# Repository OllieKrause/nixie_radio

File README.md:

# nixie_radio
A simple FM radio that uses nixie tubes to display frequency and volume. The radio does use a custom PCB so I've included the Autodesk Eagle .brd, .sch, and custom.lib files. I also included the CAM files which are compatible with JLCPCB's cheapest 2 layer PCB manufacturing service.

I want to give a huge thanks to andykarpov for his TEA5767 FM radio library which I've used extensively throughout this project. https://github.com/andykarpov/TEA5767

While the code and hardware have been tested, this project is still very much a work in progress and the user experience has yet to be optimized. 

I hope to document this project in much greater detail once I'm satisfied with the first prototype. 

Questions, comments, suggestions?
Ollie.krause@gmail.com
https://bananascience.net

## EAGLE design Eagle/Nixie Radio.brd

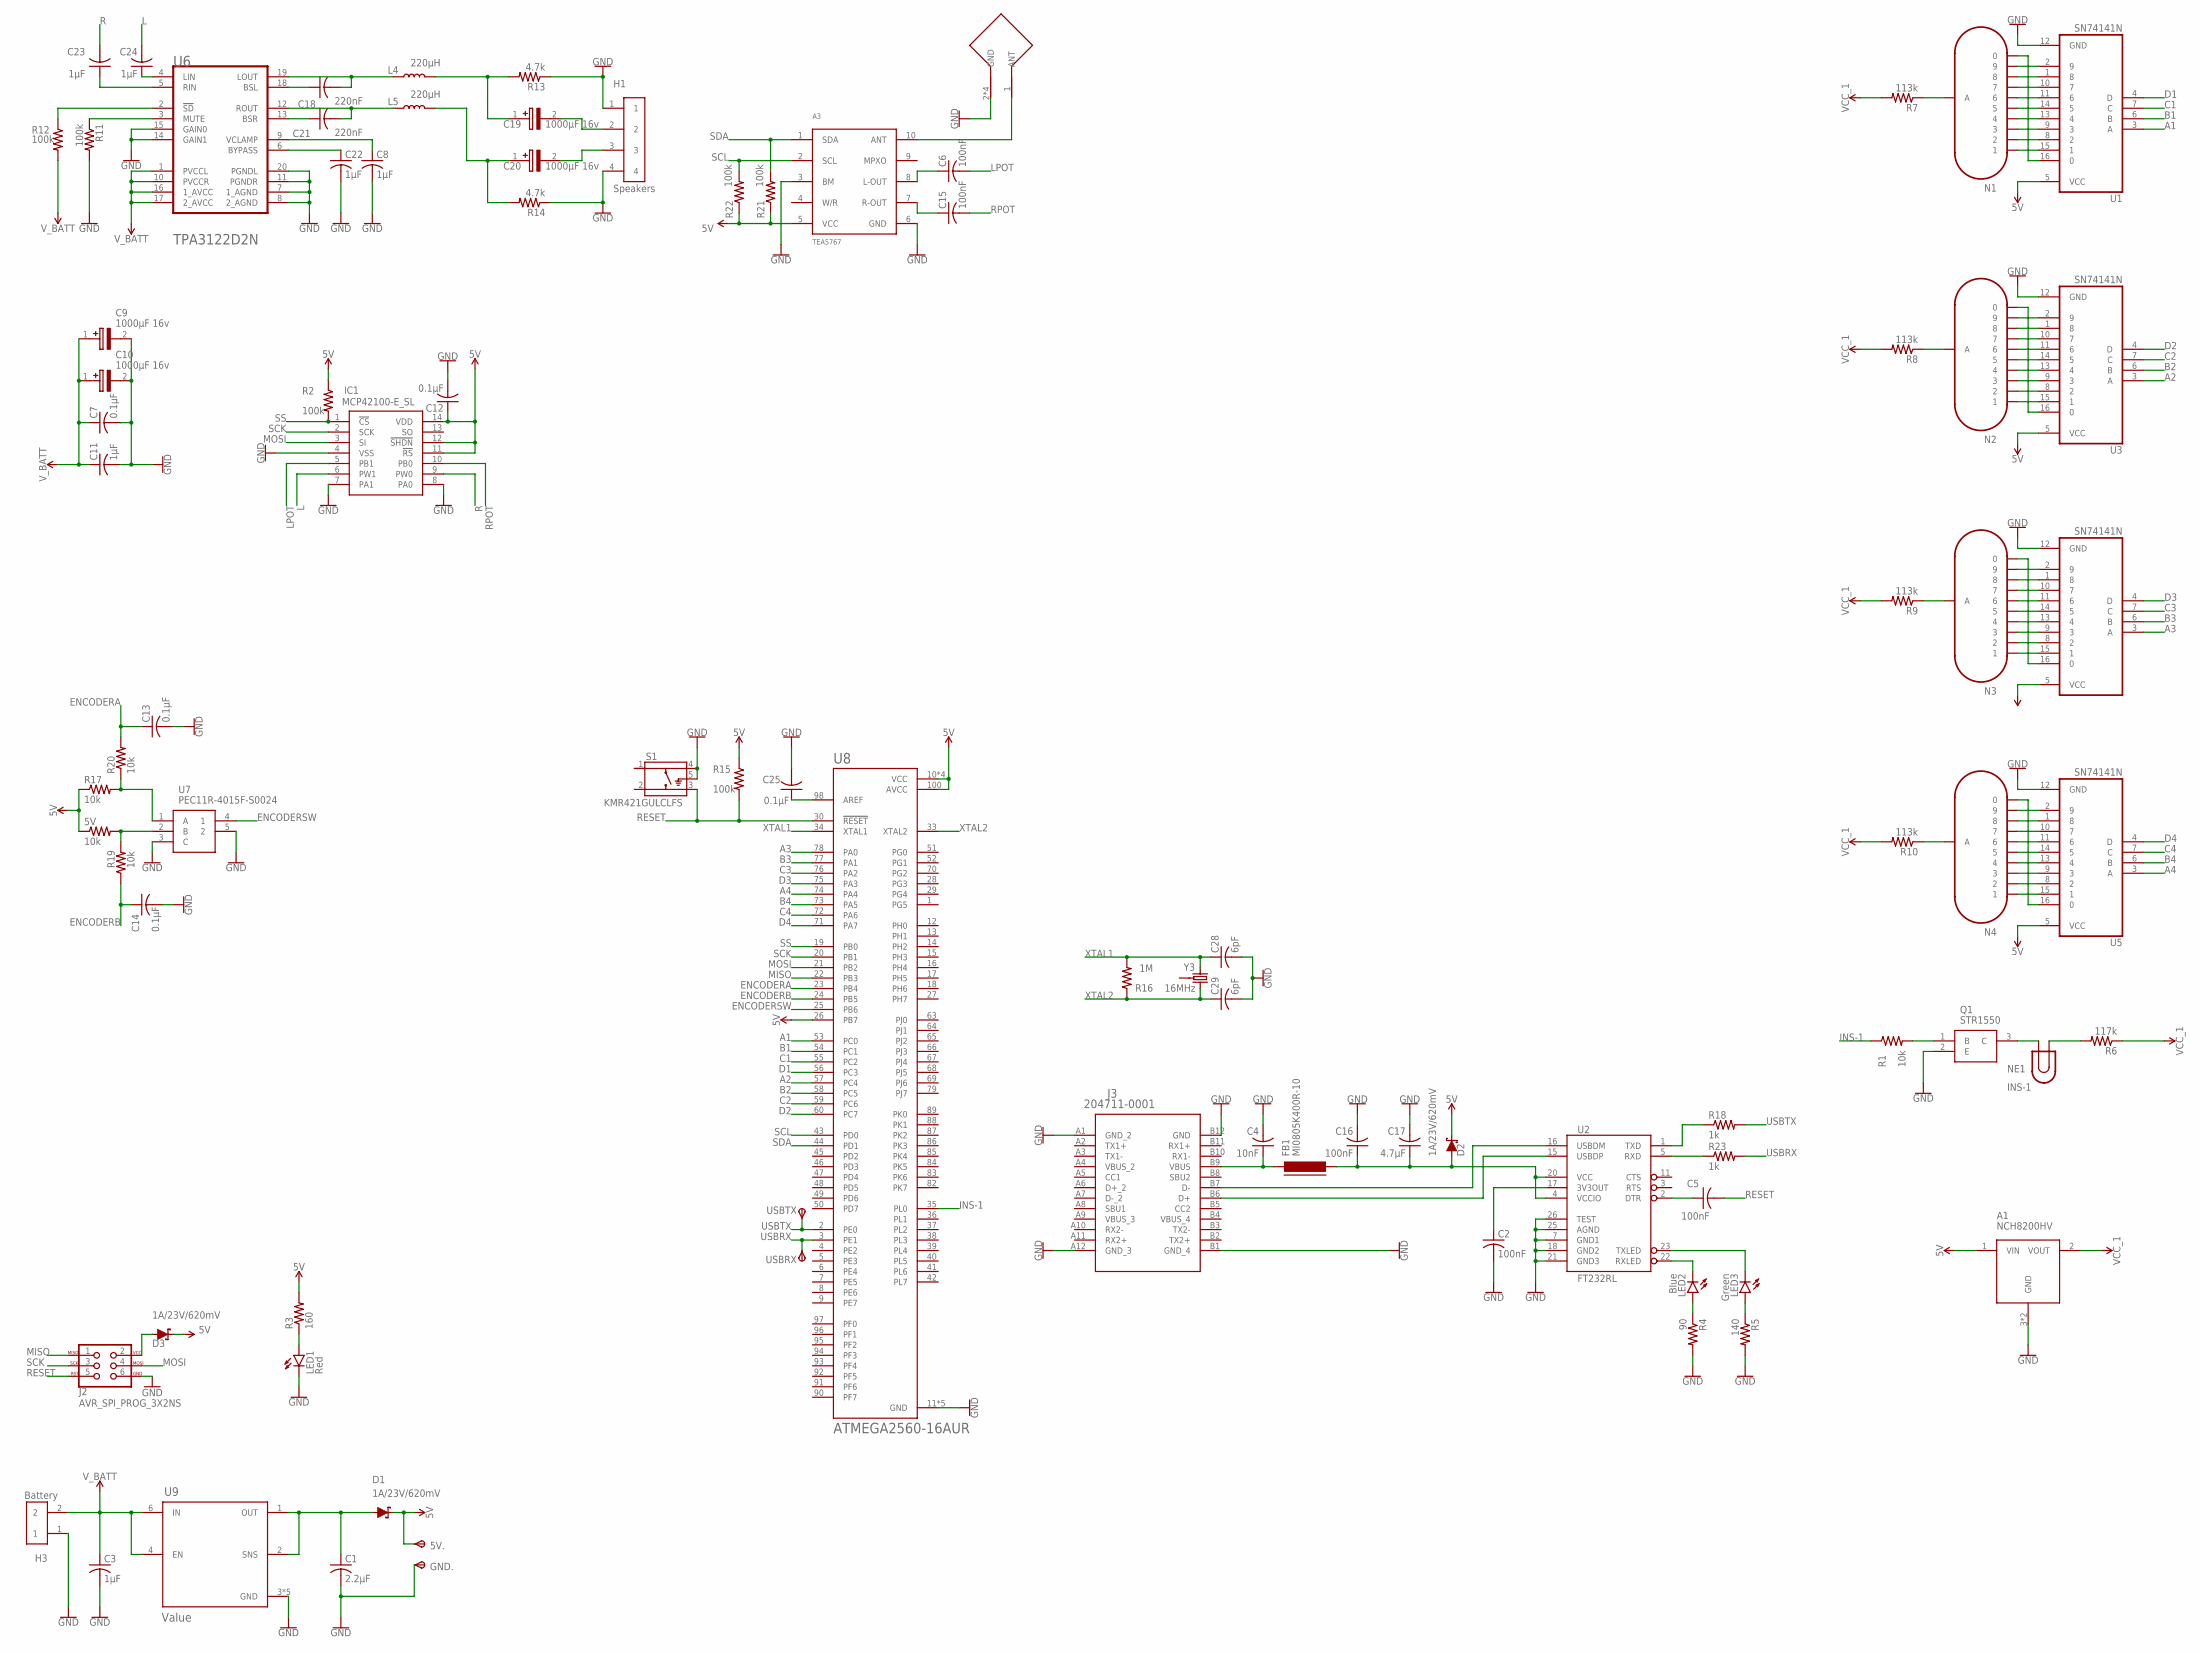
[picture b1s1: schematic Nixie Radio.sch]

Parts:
5V: 10k; M0805
5V.: TPSTP20R; TP20R
A1: NCH8200HV
A3: TEA5767
AE1: ANTENNA; RFPC-MMCX03-F
C1: 2.2µF; C0805
C2, C5, C6, C15, C16: 100nF; C0805
C3, C8, C11, C22, C23, C24: 1µF; C0805
C4: 10nF; C0805
C7, C12, C13, C14, C25: 0.1µF; C0805
C9, C10, C19, C20: 1000µF 16v; CAPAE1030X1080N
C17: 4.7µF; C0805
C18, C21: 220nF; C0805
C28, C29: 6pF; C0805
D1, D2, D3: 1A/23V/620mV; SOD-323
FB1: MI0805K400R-10; FB805
GND.: TPSTP20R; TP20R
H1: Speakers; 4_PAD_0.1"
H3: Battery; 2_PAD_0.1"
IC1: MCP42100-E_SL; SOIC127P600X175-14N
J2: AVR_SPI_PROG_3X2NS; 2X3-NS
J3: 204711-0001; 204711-0001_MOL
L4, L5: 220µH; 0207ROUND
LED1: Red; SML0805
LED2: Blue; SML0805
LED3: Green; SML0805
N1, N2, N3, N4: IN-17
NE1: INS-1
Q1: STR1550; SOT105P255X140-3N
R1, R17, R19, R20: 10k; M0805
R2, R11, R12, R15, R21, R22: 100k; M0805
R3: 160; M0805
R4: 90; M0805
R5: 140; M0805
R6: 117k; M0805
R7, R8, R9, R10: 113k; M0805
R13, R14: 4.7k; M0805
R16: 1M; M0805
R18, R23: 1k; M0805
S1: KMR421GULCLFS; SW_KMR421GULCLFS
U1, U3, U4, U5: SN74141N; DIP762W46P254L2134H508Q16
U2: FT232RL; SSOP28DB
U6: TEXAS_INSTRUMENTS_TPA3122D2NTEXAS_INSTRUMENTS_TPA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; TEXAS_INSTRUMENTS_TPA3122D2N_0
U7: PEC11R-4015F-S0024; PEC12R-4XXXF-SXXXX_1
U8: ATMEGA2560-16AUR; QFP50P1600X1600X120-100N
U9: Value; 6-WSON
USBRX: TPSTP20R; TP20R
USBTX: TPSTP20R; TP20R
Y3: 16MHz; CRYSTAL-SMD-2X2.5MM

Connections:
5V: 5V.1, 5V..TP, A1.1 (VIN), A3.5 (VCC), C12.1, D1.C, D2.C, D3.C, IC1.11 (!RS), IC1.12 (!SHDN), IC1.14 (VDD), R2.1, R3.2, R15.1, R17.1, R21.1, R22.1, U1.5 (VCC), U3.5 (VCC), U4.5 (VCC), U5.5 (VCC), U8.10 (VCC), U8.26 (PB7), U8.31 (VCC), U8.61 (VCC), U8.80 (VCC), U8.100 (AVCC)
A1: U1.3 (A), U8.53 (PC0)
A2: U3.3 (A), U8.57 (PC4)
A3: U4.3 (A), U8.78 (PA0)
A4: U5.3 (A), U8.74 (PA4)
B1: U1.6 (B), U8.54 (PC1)
B2: U3.6 (B), U8.58 (PC5)
B3: U4.6 (B), U8.77 (PA1)
B4: U5.6 (B), U8.73 (PA5)
C1: U1.7 (C), U8.55 (PC2)
C2: U3.7 (C), U8.59 (PC6)
C3: U4.7 (C), U8.76 (PA2)
C4: U5.7 (C), U8.72 (PA6)
D1: U1.4 (D), U8.56 (PC3)
D2: U3.4 (D), U8.60 (PC7)
D3: U4.4 (D), U8.75 (PA3)
D4: U5.4 (D), U8.71 (PA7)
ENCODERA: C13.1, R20.2, U8.23 (PB4)
ENCODERB: C14.1, R19.1, U8.24 (PB5)
ENCODERSW: U7.4 (1), U8.25 (PB6)
GND: A1.3 (GND), A1.4 (GND), A3.3 (BM), A3.6 (GND), AE1.2 (GND), AE1.3 (GND), AE1.4 (GND), AE1.5 (GND), C1.2, C2.2, C3.2, C4.2, C7.2, C8.2, C9.2 (-), C10.2 (-), C11.2, C12.2, C13.2, C14.2, C16.2, C17.2, C22.2, C25.2, C28.2, C29.2, GND..TP, H1.1, H1.4, H3.1, IC1.4 (VSS), IC1.7 (PA1), IC1.8 (PA0), J2.6, J3.A1 (GND_2), J3.A12 (GND_3), J3.B1 (GND_4), J3.B12 (GND), LED1.C, Q1.2 (E), R4.2, R5.2, R11.2, R13.1, R14.1, S1.4, S1.5 (G), U1.12 (GND), U2.7 (GND1), U2.18 (GND2), U2.21 (GND3), U2.25 (AGND), U2.26 (TEST), U3.12 (GND), U4.12 (GND), U5.12 (GND), U6.7 (1_AGND), U6.8 (2_AGND), U6.11 (PGNDR), U6.14 (GAIN1), U6.15 (GAIN0), U6.20 (PGNDL), U7.3 (C), U7.5 (2), U8.11 (GND), U8.32 (GND), U8.62 (GND), U8.81 (GND), U8.99 (GND), U9.3 (GND), U9.5 (GND), U9.7 (GND), U9.8 (GND), U9.9 (GND), Y3.P2 (GND), Y3.P4 (GND)
INS-1: R1.1, U8.35 (PL0)
L: C24.2, IC1.6 (PW1)
LPOT: C6.2, IC1.5 (PB1)
MISO: J2.1, U8.22 (PB3)
MOSI: IC1.3 (SI), J2.4, U8.21 (PB2)
unnamed: C4.1, FB1.1, J3.B9 (VBUS)
unnamed: NE1.2, Q1.3 (C)
unnamed: NE1.1, R6.2
unnamed: C5.1, U2.2 (DTR)
unnamed: C2.1, U2.17 (3V3OUT)
unnamed: LED1.A, R3.1
unnamed: C16.1, C17.1, D2.A, FB1.2, U2.4 (VCCIO), U2.20 (VCC)
unnamed: C1.1, D1.A, U9.1 (OUT), U9.2 (SNS)
unnamed: Q1.1 (B), R1.2
unnamed: N1.1, U1.15 (1)
unnamed: J3.B6 (D+), U2.15 (USBDP)
unnamed: J3.B7 (D-), U2.16 (USBDM)
unnamed: R18.1, U2.1 (TXD)
unnamed: N1.2, U1.8 (2)
unnamed: N1.3, U1.9 (3)
unnamed: N1.4, U1.13 (4)
unnamed: N1.5, U1.14 (5)
unnamed: N1.6, U1.11 (6)
unnamed: N1.7, U1.10 (7)
unnamed: N1.8, U1.1 (8)
unnamed: N1.9, U1.2 (9)
unnamed: N1.0, U1.16 (0)
unnamed: N1.A, R7.1
unnamed: N2.1, U3.15 (1)
unnamed: N2.2, U3.8 (2)
unnamed: N2.3, U3.9 (3)
unnamed: N2.4, U3.13 (4)
unnamed: N2.5, U3.14 (5)
unnamed: N2.6, U3.11 (6)
unnamed: N2.7, U3.10 (7)
unnamed: N2.8, U3.1 (8)
unnamed: N2.9, U3.2 (9)
unnamed: N2.0, U3.16 (0)
unnamed: N2.A, R8.1
unnamed: N3.1, U4.15 (1)
unnamed: N3.2, U4.8 (2)
unnamed: N3.3, U4.9 (3)
unnamed: N3.4, U4.13 (4)
unnamed: N3.5, U4.14 (5)
unnamed: N3.6, U4.11 (6)
unnamed: N3.7, U4.10 (7)
unnamed: N3.8, U4.1 (8)
unnamed: N3.9, U4.2 (9)
unnamed: N3.0, U4.16 (0)
unnamed: N3.A, R9.1
unnamed: N4.1, U5.15 (1)
unnamed: N4.2, U5.8 (2)
unnamed: N4.3, U5.9 (3)
unnamed: N4.4, U5.13 (4)
unnamed: N4.5, U5.14 (5)
unnamed: N4.6, U5.11 (6)
unnamed: N4.7, U5.10 (7)
unnamed: N4.8, U5.1 (8)
unnamed: N4.9, U5.2 (9)
unnamed: N4.0, U5.16 (0)
unnamed: N4.A, R10.1
unnamed: LED2.A, R4.1
unnamed: C8.1, U6.9 (VCLAMP)
unnamed: A3.10 (ANT), AE1.1 (ANT)
unnamed: R11.1, U6.3 (MUTE)
unnamed: R12.1, U6.2 (!SD!)
unnamed: R23.1, U2.5 (RXD)
unnamed: C18.2, L4.1, U6.19 (LOUT)
unnamed: C18.1, U6.18 (BSL)
unnamed: C19.2 (-), H1.2
unnamed: C20.1 (+), L5.2, R14.2
unnamed: C20.2 (-), H1.3
unnamed: C21.1, U6.13 (BSR)
unnamed: LED2.C, U2.22 (RXLED)
unnamed: C22.1, U6.6 (BYPASS)
unnamed: C23.1, U6.5 (RIN)
unnamed: C24.1, U6.4 (LIN)
unnamed: C19.1 (+), L4.2, R13.2
unnamed: C21.2, L5.1, U6.12 (ROUT)
unnamed: LED3.C, U2.23 (TXLED)
unnamed: C25.1, U8.98 (AREF)
unnamed: R17.2, R20.1, U7.1 (A)
unnamed: LED3.A, R5.1
unnamed: 5V.2, R19.2, U7.2 (B)
unnamed: A3.8 (L-OUT), C6.1
unnamed: A3.7 (R-OUT), C15.1
unnamed: D3.A, J2.2
R: C23.2, IC1.9 (PW0)
RESET: C5.2, J2.5, R15.2, S1.3, U8.30 (!RESET)
RPOT: C15.2, IC1.10 (PB0)
SCK: IC1.2 (SCK), J2.3, U8.20 (PB1)
SCL: A3.2 (SCL), R22.2, U8.43 (PD0)
SDA: A3.1 (SDA), R21.2, U8.44 (PD1)
SS: IC1.1 (!CS), R2.2, U8.19 (PB0)
USBRX: R23.2, U8.3 (PE1), USBRX.TP
USBTX: R18.2, U8.2 (PE0), USBTX.TP
VBUS_2: J3.A4 (VBUS_2)
VBUS_3: J3.A9 (VBUS_3)
VBUS_4: J3.B4 (VBUS_4)
VCC_1: A1.2 (VOUT), R6.1, R7.2, R8.2, R9.2, R10.2
V_BATT: C3.1, C7.1, C9.1 (+), C10.1 (+), C11.1, H3.2, R12.2, U6.1 (PVCCL), U6.10 (PVCCR), U6.16 (1_AVCC), U6.17 (2_AVCC), U9.4 (EN), U9.6 (IN)
XTAL1: C28.1, R16.2, U8.34 (XTAL1), Y3.P1 (1)
XTAL2: C29.1, R16.1, U8.33 (XTAL2), Y3.P3 (2)

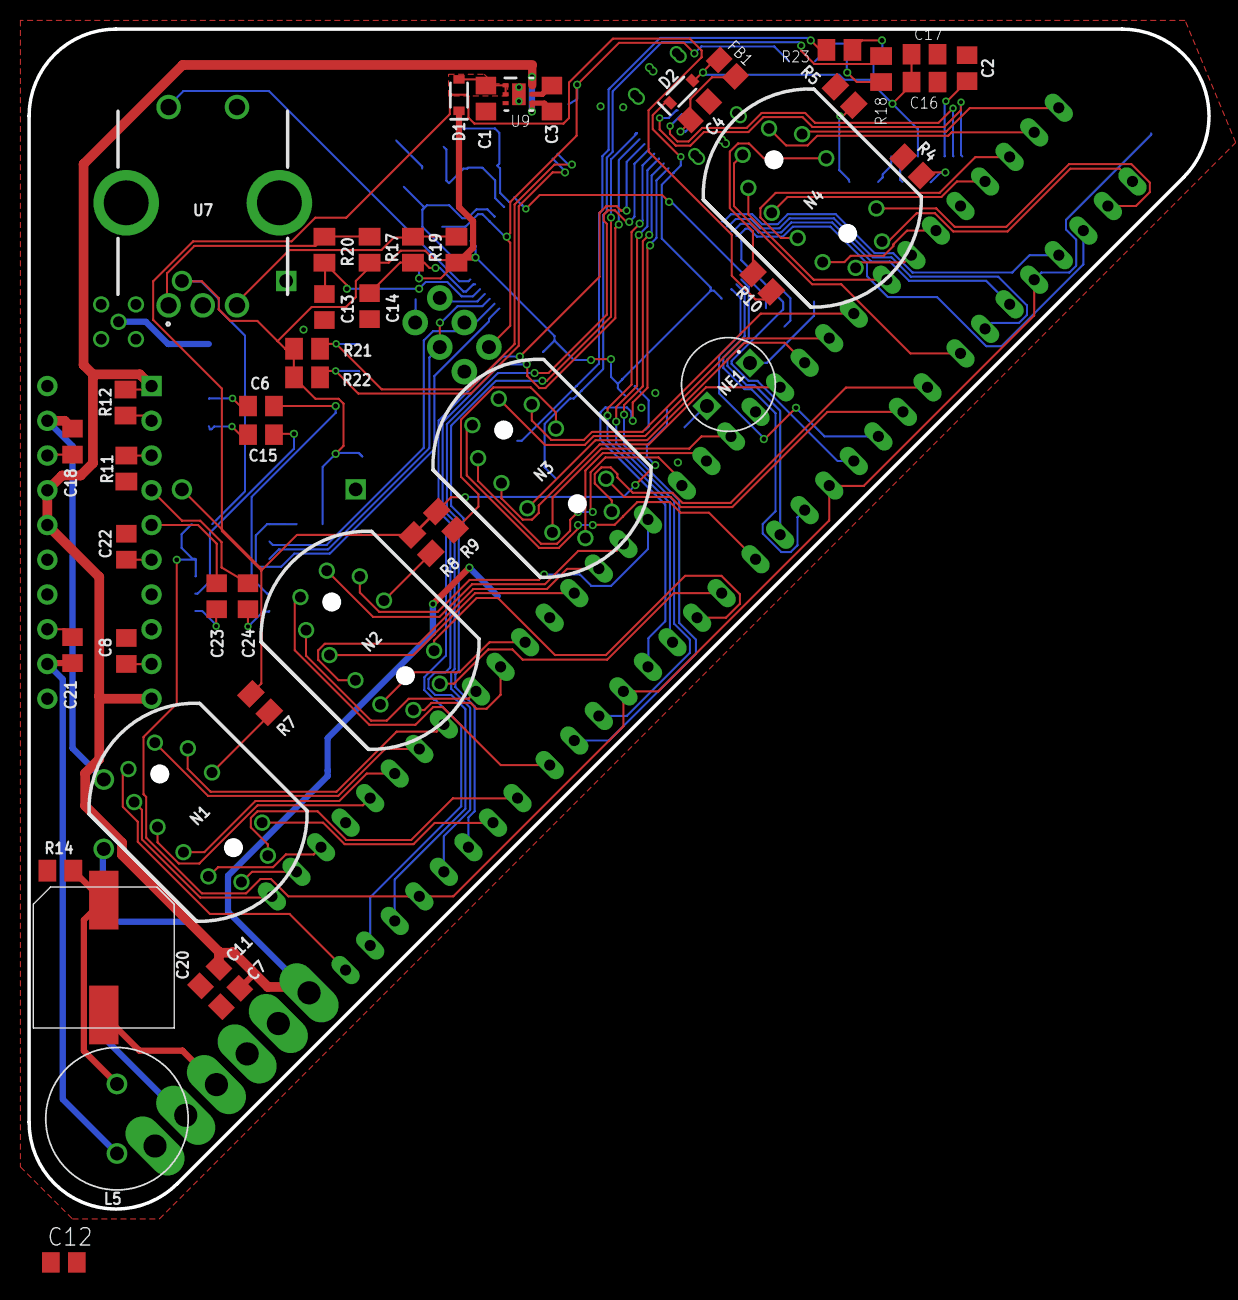
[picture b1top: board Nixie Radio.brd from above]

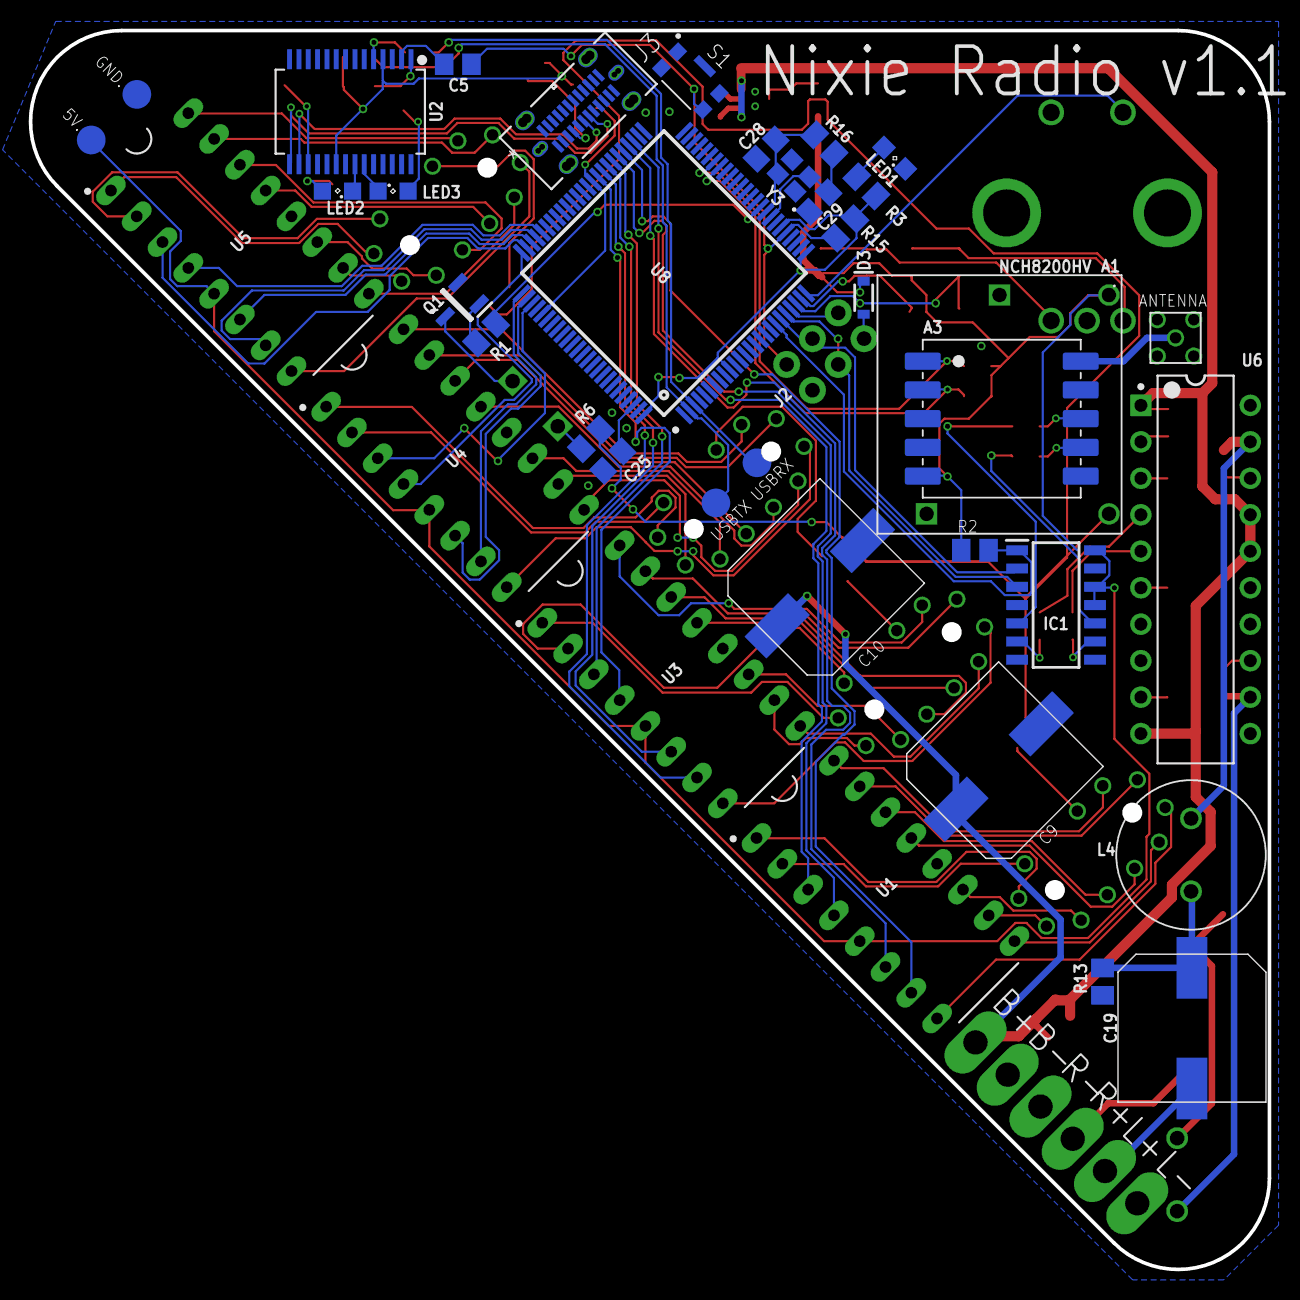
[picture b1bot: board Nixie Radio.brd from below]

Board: 2 copper layers, 86.3 x 86.3 mm, 89 parts (41 on the bottom side), 121 nets.

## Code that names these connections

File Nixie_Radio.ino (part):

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#include <SPI.h>

// Rotary encoder inputs
#define encoderA 10
#define encoderB 11
#define encoderSW 12

// Number of nixie tubes (number of digits)
#define digits 4
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
  changeFrequency(); // Tune radio to recovered frequency

  pinMode(encoderA, INPUT); // Set encoder pins as inputs
  pinMode(encoderB, INPUT);
  pinMode(encoderSW, INPUT_PULLUP);

  pinMode(potCs, OUTPUT); // Configure pot chip select as output
  digitalWrite(potCs, HIGH); // Pot chip select default to de-selected
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

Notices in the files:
Nixie_Radio.ino:
License: Creative Commons Non Commercial
parts and their libraries:
SparkFun-Connectors: Licensing: Creative Commons ShareAlike 4.0 International - https://creativecommons.org/licenses/by-sa/4.0
COPYRIGHT: Copyright (C) 2018 Accelerated Designs. All rights reserved
